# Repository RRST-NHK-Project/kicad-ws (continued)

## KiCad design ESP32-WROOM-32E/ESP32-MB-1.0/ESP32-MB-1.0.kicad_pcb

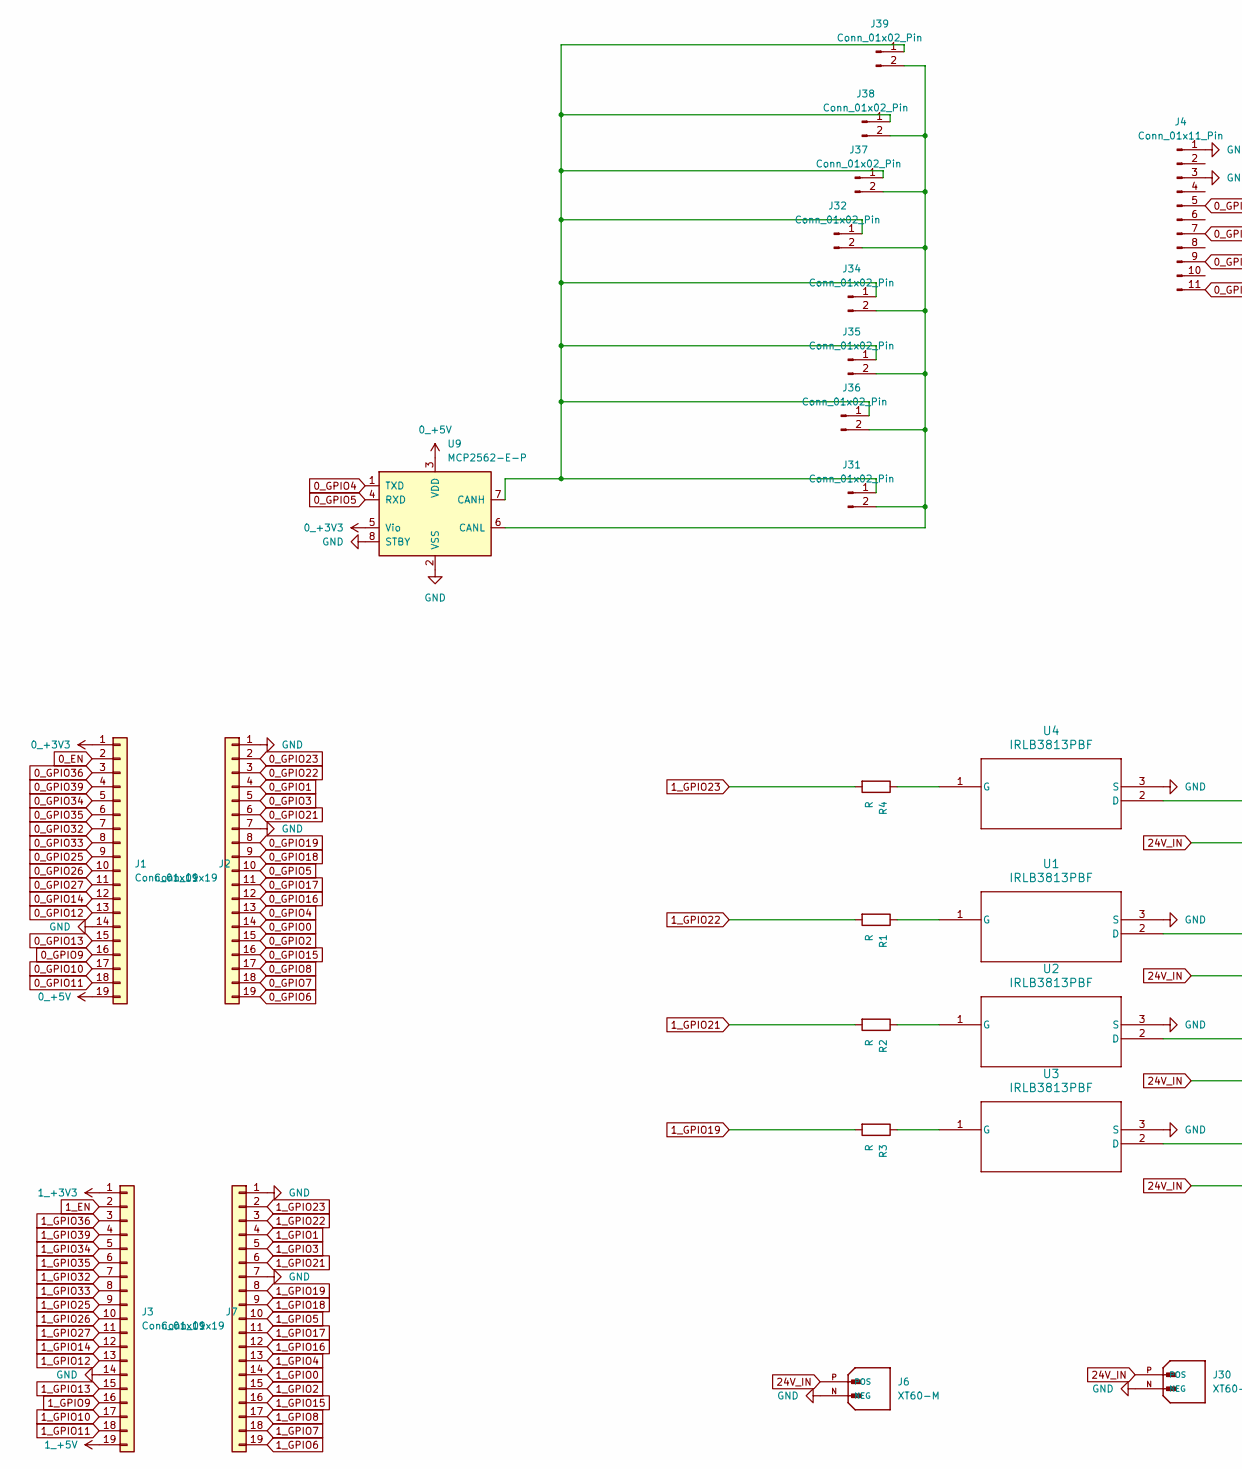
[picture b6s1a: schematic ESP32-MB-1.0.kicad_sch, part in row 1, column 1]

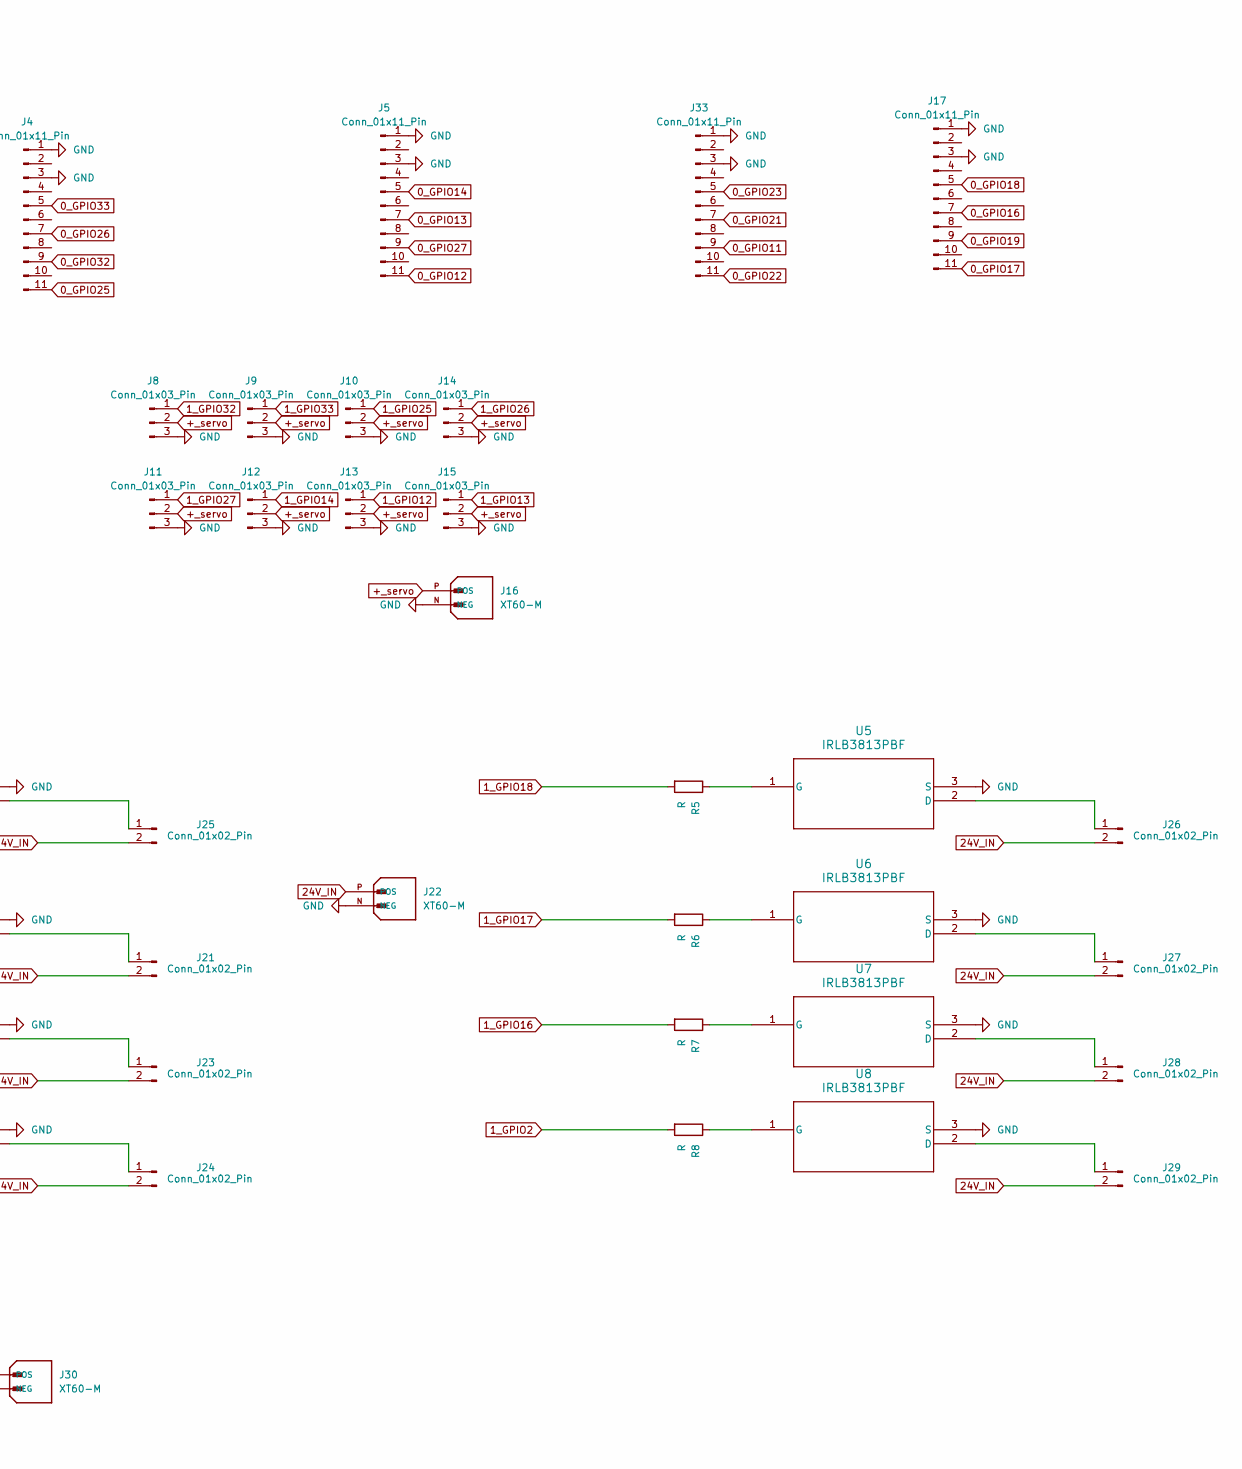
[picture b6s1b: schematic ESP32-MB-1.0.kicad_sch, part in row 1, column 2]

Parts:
J1, J2, J3, J7: Conn_01x19; PinSocket_1x19_P2.54mm_Vertical
J4, J5, J17, J33: Conn_01x11_Pin; PinHeader_1x11_P2.54mm_Vertical
J6, J30: XT60-M; AMASS_XT60-F_1x02_P7.20mm_Vertical; PARTREV V1.2
J8, J9, J10, J11, J12, J13, J14, J15: Conn_01x03_Pin; JST_XH_B3B-XH-AM_1x03_P2.50mm_Vertical
J16, J22: XT60-M; AMASS_XT60-M_1x02_P7.20mm_Vertical; PARTREV V1.2
J21, J23, J24, J25, J26, J27, J28, J29, J31, J32, J34, J35, J36, J37, J38, J39: Conn_01x02_Pin; JST_XH_B2B-XH-AM_1x02_P2.50mm_Vertical
R1, R2, R3, R4, R5, R6, R7, R8: R; R_Axial_DIN0207_L6.3mm_D2.5mm_P10.16mm_Horizontal
U1, U2, U3, U4, U5, U6, U7, U8: IRLB3813PBF; PG-TO220-3_INF
U9: MCP2562-E-P; DIP-8_W7.62mm

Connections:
0_+3V3: J1.1, U9.5 (Vio)
0_+5V: J1.19, U9.3 (VDD)
0_EN: J1.2
0_GPIO0: J2.14
0_GPIO1: J2.4
0_GPIO2: J2.15
0_GPIO3: J2.5
0_GPIO4: J2.13, U9.1 (TXD)
0_GPIO5: J2.10, U9.4 (RXD)
0_GPIO6: J2.19
0_GPIO7: J2.18
0_GPIO8: J2.17
0_GPIO9: J1.16
0_GPIO10: J1.17
0_GPIO11: J1.18, J33.9
0_GPIO12: J1.13, J5.11
0_GPIO13: J1.15, J5.7
0_GPIO14: J1.12, J5.5
0_GPIO15: J2.16
0_GPIO16: J2.12, J17.7
0_GPIO17: J2.11, J17.11
0_GPIO18: J2.9, J17.5
0_GPIO19: J2.8, J17.9
0_GPIO21: J2.6, J33.7
0_GPIO22: J2.3, J33.11
0_GPIO23: J2.2, J33.5
0_GPIO25: J1.9, J4.11
0_GPIO26: J1.10, J4.7
0_GPIO27: J1.11, J5.9
0_GPIO32: J1.7, J4.9
0_GPIO33: J1.8, J4.5
0_GPIO34: J1.5
0_GPIO35: J1.6
0_GPIO36: J1.3
0_GPIO39: J1.4
1_+3V3: J3.1
1_+5V: J3.19
1_EN: J3.2
1_GPIO0: J7.14
1_GPIO1: J7.4
1_GPIO2: J7.15, R8.2
1_GPIO3: J7.5
1_GPIO4: J7.13
1_GPIO5: J7.10
1_GPIO6: J7.19
1_GPIO7: J7.18
1_GPIO8: J7.17
1_GPIO9: J3.16
1_GPIO10: J3.17
1_GPIO11: J3.18
1_GPIO12: J3.13, J13.1
1_GPIO13: J3.15, J15.1
1_GPIO14: J3.12, J12.1
1_GPIO15: J7.16
1_GPIO16: J7.12, R7.2
1_GPIO17: J7.11, R6.2
1_GPIO18: J7.9, R5.2
1_GPIO19: J7.8, R3.2
1_GPIO21: J7.6, R2.2
1_GPIO22: J7.3, R1.2
1_GPIO23: J7.2, R4.2
1_GPIO25: J3.9, J10.1
1_GPIO26: J3.10, J14.1
1_GPIO27: J3.11, J11.1
1_GPIO32: J3.7, J8.1
1_GPIO33: J3.8, J9.1
1_GPIO34: J3.5
1_GPIO35: J3.6
1_GPIO36: J3.3
1_GPIO39: J3.4
24V_IN: J6.P (POS), J21.2, J22.P (POS), J23.2, J24.2, J25.2, J26.2, J27.2, J28.2, J29.2, J30.P (POS)
+_servo: J8.2, J9.2, J10.2, J11.2, J12.2, J13.2, J14.2, J15.2, J16.P (POS)
GND: J1.14, J2.1, J2.7, J3.14, J4.1, J4.3, J5.1, J5.3, J6.N (NEG), J7.1, J7.7, J8.3, J9.3, J10.3, J11.3, J12.3, J13.3, J14.3, J15.3, J16.N (NEG), J17.1, J17.3, J22.N (NEG), J30.N (NEG), J33.1, J33.3, U1.3 (S), U2.3 (S), U3.3 (S), U4.3 (S), U5.3 (S), U6.3 (S), U7.3 (S), U8.3 (S), U9.2 (VSS), U9.8 (STBY)
unnamed: J21.1, U1.2 (D)
unnamed: J23.1, U2.2 (D)
unnamed: J24.1, U3.2 (D)
unnamed: J25.1, U4.2 (D)
unnamed: J26.1, U5.2 (D)
unnamed: J27.1, U6.2 (D)
unnamed: J28.1, U7.2 (D)
unnamed: J29.1, U8.2 (D)
unnamed: J31.1, J32.1, J34.1, J35.1, J36.1, J37.1, J38.1, J39.1, U9.7 (CANH)
unnamed: J31.2, J32.2, J34.2, J35.2, J36.2, J37.2, J38.2, J39.2, U9.6 (CANL)
unnamed: R1.1, U1.1 (G)
unnamed: R2.1, U2.1 (G)
unnamed: R3.1, U3.1 (G)
unnamed: R4.1, U4.1 (G)
unnamed: R5.1, U5.1 (G)
unnamed: R6.1, U6.1 (G)
unnamed: R7.1, U7.1 (G)
unnamed: R8.1, U8.1 (G)

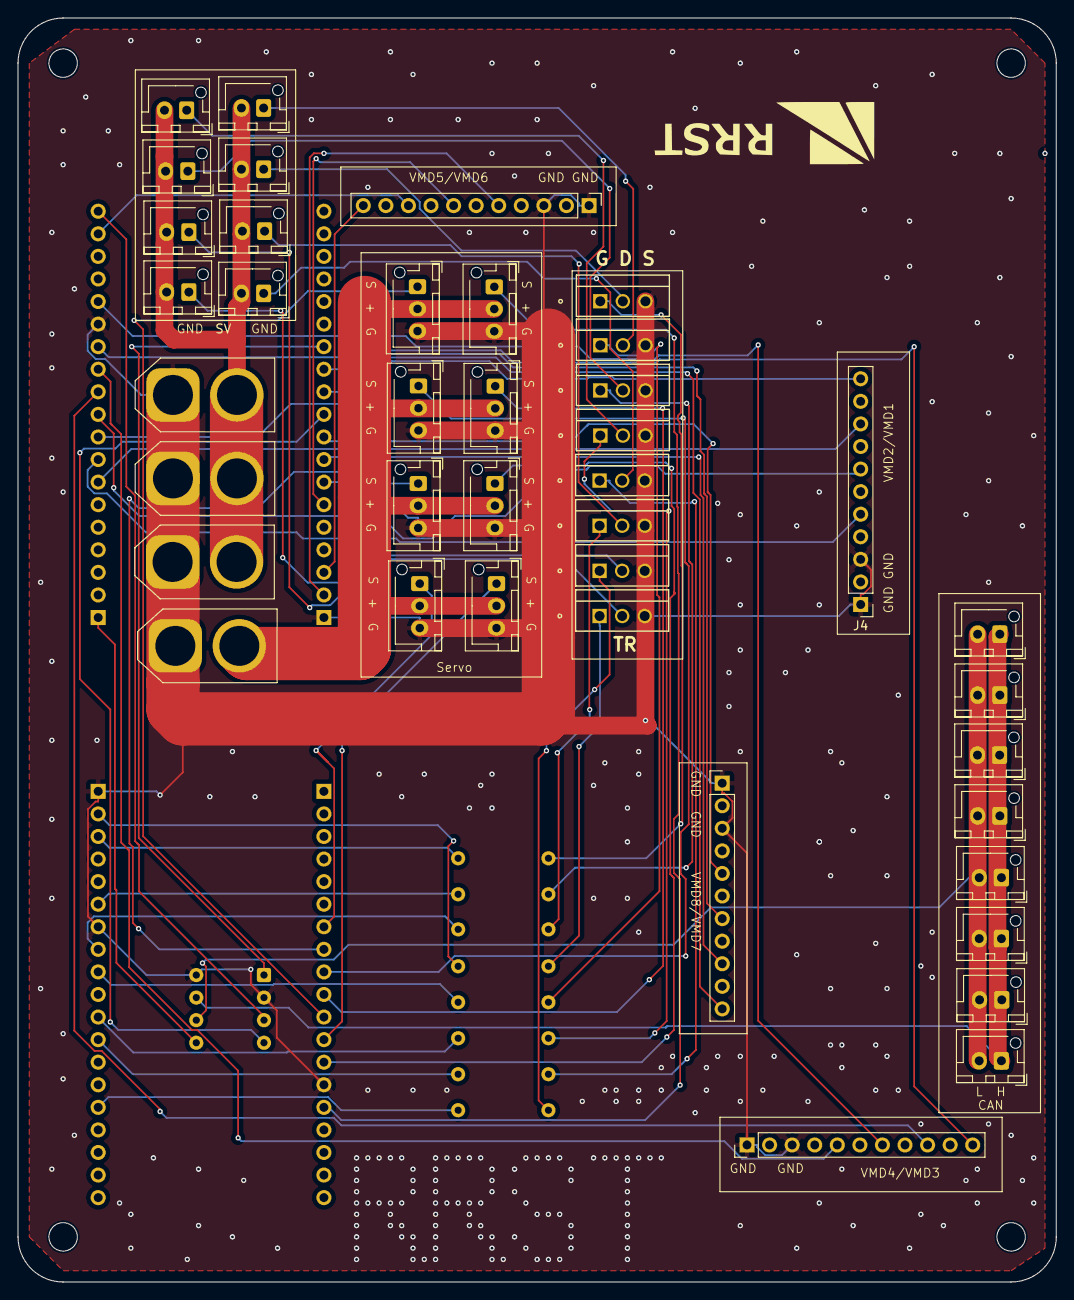
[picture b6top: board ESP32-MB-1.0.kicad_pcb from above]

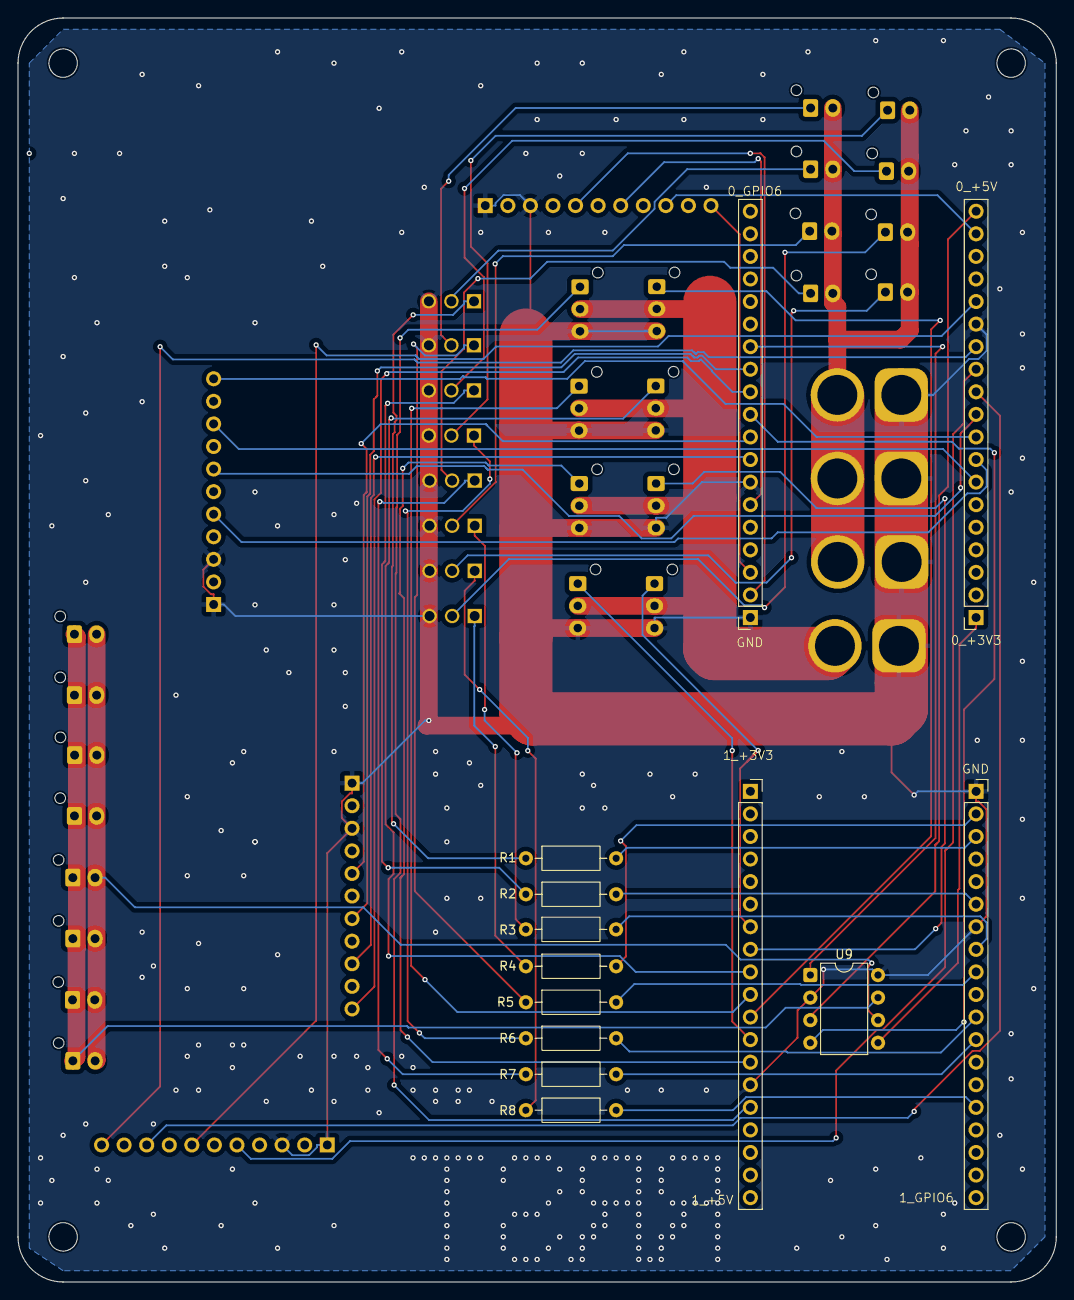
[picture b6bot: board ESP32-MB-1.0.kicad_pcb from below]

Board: 2 copper layers, 116.8 x 142.2 mm, 56 parts (13 on the bottom side), 57 nets.

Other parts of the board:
REF1, REF2, REF3: MountingHole_3.2mm_M3
